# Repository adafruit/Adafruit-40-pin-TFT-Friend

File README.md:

## Adafruit-40-pin-TFT-Friend

<a href="http://www.adafruit.com/products/1932"><br/>
Click here to purchase one from the Adafruit shop</a>

These are the Eagle CAD files for the Adafruit 40-pin TFT Friend / Breakout Board
- https://www.adafruit.com/product/1932

This breakout board is something we designed in-house to help us work with 'dot-clock' 40-pin TFT displays that require the RGB pixel data to be clocked in continuously. These displays have 40-pin Flex PCB (FPC) cables and often require a boost converter for the backlight LED, which makes them annoying to breadboard. To make them breadboardable, we stuck a 40-pin FPC and a FAN5333-based backlight driver with adjustable current onto a labeled breakout board. Now you can poke and probe each pin!

The backlight driver defaults to 25mA and can boost up to 24VDC for up to 7-LED strings. Check your display datasheet for the string configuration, and short out the jumpers to increase the backlight current. 

### License

Adafruit invests time and resources providing this open source design, please support Adafruit and open-source hardware by purchasing products from [Adafruit.com](https://www.adafruit.com)!

Creative Commons Attribution, Share-Alike license, check license.txt for more information All text above must be included in any redistribution - 
See license.txt for more information.

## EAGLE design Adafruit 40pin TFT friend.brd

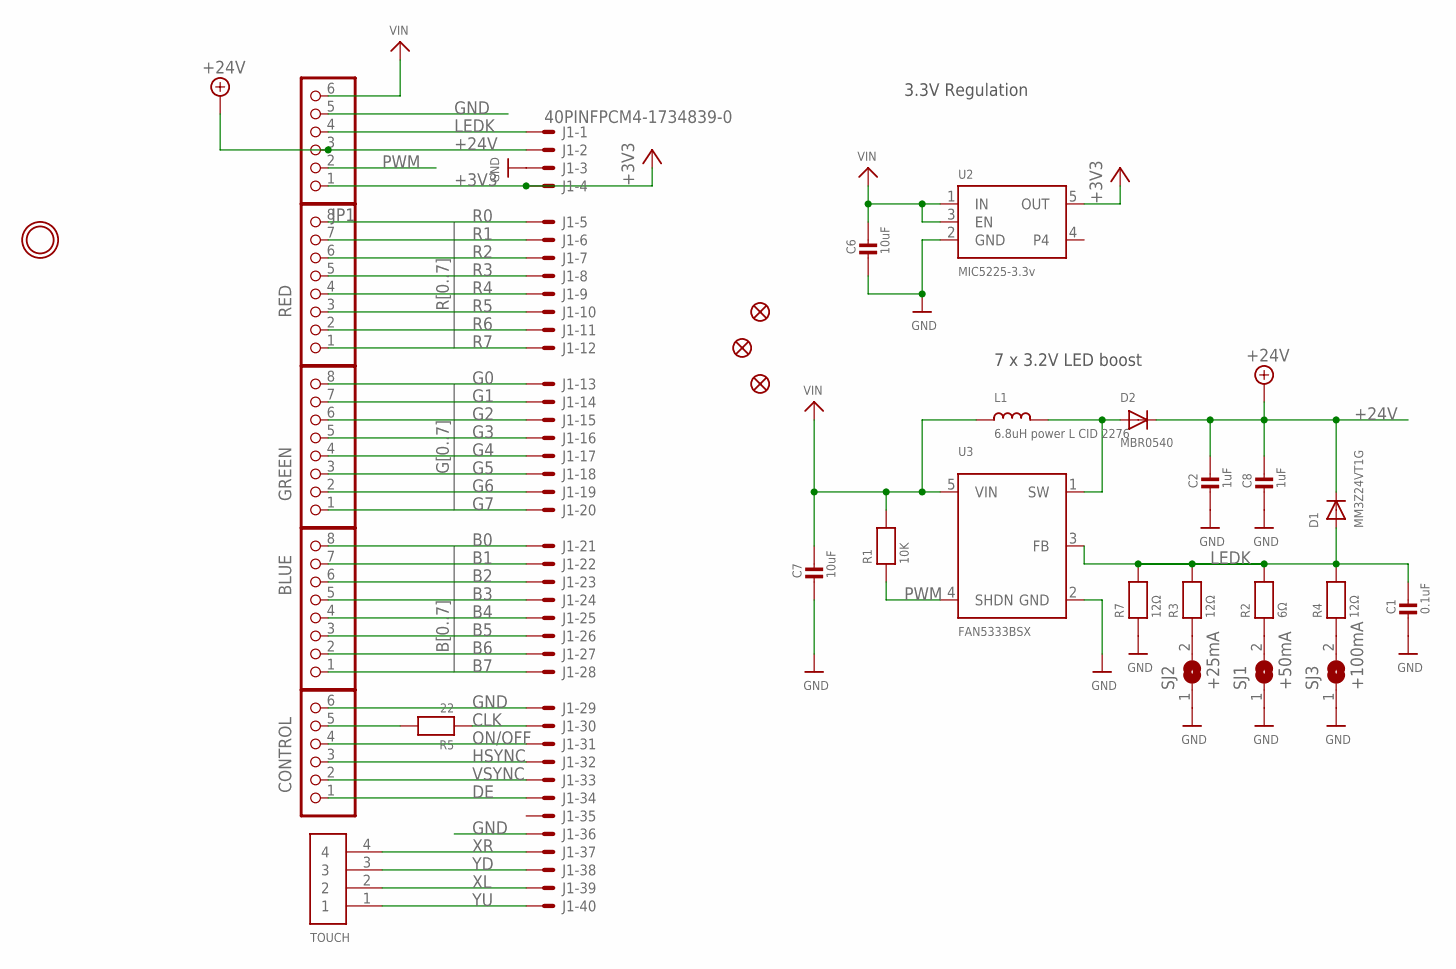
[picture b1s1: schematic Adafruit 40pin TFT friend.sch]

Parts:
BLUE: PINHD-1X8BIG; 1X08-BIG
C1: 0.1uF; _0805MP
C2, C8: 1uF; _0805MP
C6, C7: 10uF; _0805MP
CONTROL: PINHD-1X6B; 1X06-BIG
D1: MM3Z24VT1G; SMADIODE
D2: MBR0540; SOD-123
FID1, FID2, FID3: FIDUCIAL""; FIDUCIAL_1MM
GREEN: PINHD-1X8BIG; 1X08-BIG
J1: 40PINFPCM4-1734839-0; 4-1734839-0
JP1: PINHD-1X6B; 1X06-BIG
L1: 6.8uH power L CID 2276; INDUCTOR_5X5MM_NR5040_NOTHERMALS
R1: 10K; _0805MP
R2: 6Ω; _0805MP
R3, R4, R7: 12Ω; _0805MP
R5: 22; _0805MP
RED: PINHD-1X8BIG; 1X08-BIG
SJ1: +50mA; SOLDERJUMPER_ARROW_NOPASTE
SJ2: +25mA; SOLDERJUMPER_ARROW_NOPASTE
SJ3: +100mA; SOLDERJUMPER_ARROW_NOPASTE
TOUCH: 1X4-BIG; 1X04-BIG
U2: MIC5225-3.3v; SOT23-5
U3: FAN5333BSX; SOT23-5@1
U$7: MOUNTINGHOLE2.5; MOUNTINGHOLE_2.5_PLATED

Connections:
+3V3: J1.4 (MS), JP1.1, U2.5 (OUT)
+24V: C2.1, C8.1, D1.C, D2.C, J1.2 (MS), JP1.3
B0: BLUE.8, J1.21 (MS)
B1: BLUE.7, J1.22 (MS)
B2: BLUE.6, J1.23 (MS)
B3: BLUE.5, J1.24 (MS)
B4: BLUE.4, J1.25 (MS)
B5: BLUE.3, J1.26 (MS)
B6: BLUE.2, J1.27 (MS)
B7: BLUE.1, J1.28 (MS)
CLK: J1.30 (MS), R5.1
DE: CONTROL.1, J1.34 (MS)
G0: GREEN.8, J1.13 (MS)
G1: GREEN.7, J1.14 (MS)
G2: GREEN.6, J1.15 (MS)
G3: GREEN.5, J1.16 (MS)
G4: GREEN.4, J1.17 (MS)
G5: GREEN.3, J1.18 (MS)
G6: GREEN.2, J1.19 (MS)
G7: GREEN.1, J1.20 (MS)
GND: C1.2, C2.2, C6.2, C7.2, C8.2, CONTROL.6, J1.3 (MS), J1.29 (MS), J1.36 (MS), JP1.5, R7.1, SJ1.1, SJ2.1, SJ3.1, U2.2 (GND), U3.2 (GND)
HSYNC: CONTROL.3, J1.32 (MS)
LEDK: C1.1, D1.A, J1.1 (MSV), JP1.4, R2.2, R3.2, R4.2, R7.2, U3.3 (FB)
unnamed: R2.1, SJ1.2
unnamed: R3.1, SJ2.2
unnamed: R4.1, SJ3.2
unnamed: CONTROL.5, R5.2
unnamed: D2.A, L1.P$2 (2), U3.1 (SW)
ON/OFF: CONTROL.4, J1.31 (MS)
PWM: JP1.2, R1.1, U3.4 (SHDN)
R0: J1.5 (MS), RED.8
R1: J1.6 (MS), RED.7
R2: J1.7 (MS), RED.6
R3: J1.8 (MS), RED.5
R4: J1.9 (MS), RED.4
R5: J1.10 (MS), RED.3
R6: J1.11 (MS), RED.2
R7: J1.12 (MS), RED.1
VIN: C6.1, C7.1, JP1.6, L1.P$1 (1), R1.2, U2.1 (IN), U2.3 (EN), U3.5 (VIN)
VSYNC: CONTROL.2, J1.33 (MS)
XL: J1.39 (MS), TOUCH.2
XR: J1.37 (MS), TOUCH.4
YD: J1.38 (MS), TOUCH.3
YU: J1.40 (MS), TOUCH.1

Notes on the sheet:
7 x 3.2V LED boost
3.3V Regulation

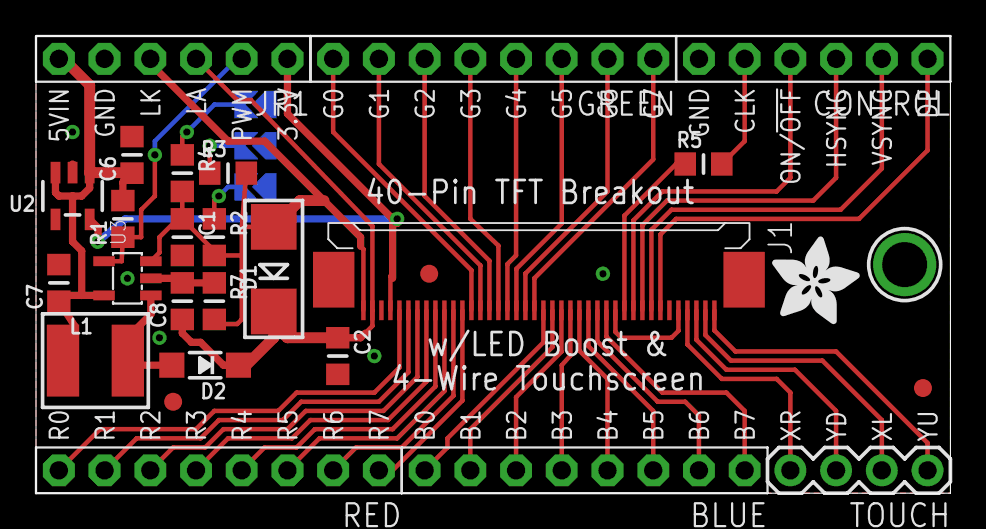
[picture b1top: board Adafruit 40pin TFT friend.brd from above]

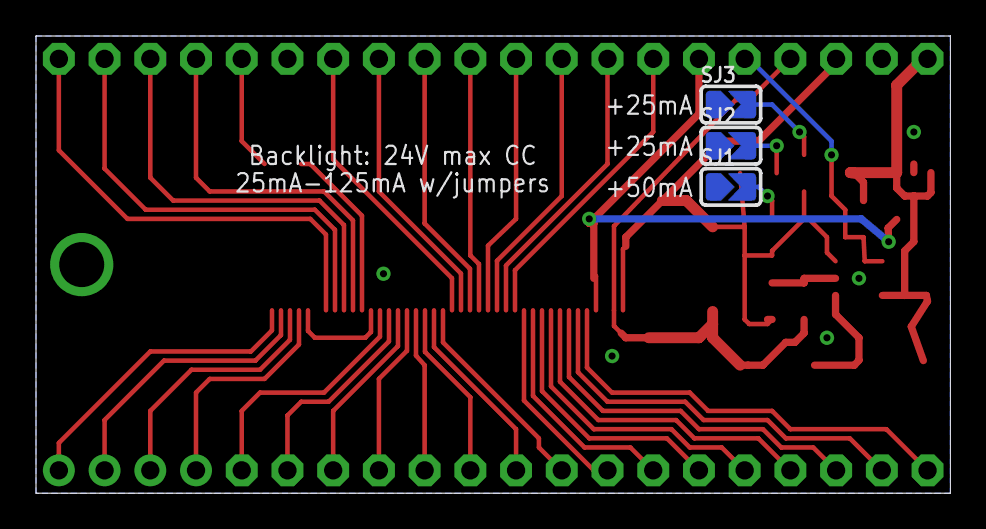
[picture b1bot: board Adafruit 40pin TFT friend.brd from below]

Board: 2 copper layers, 50.8 x 25.4 mm, 31 parts (3 on the bottom side), 44 nets.

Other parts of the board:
U$15: ADAFRUIT_5MM

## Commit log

2014-06-16 init
2014-06-16 fix url
2015-12-07 Corrected product code in URL in README.
